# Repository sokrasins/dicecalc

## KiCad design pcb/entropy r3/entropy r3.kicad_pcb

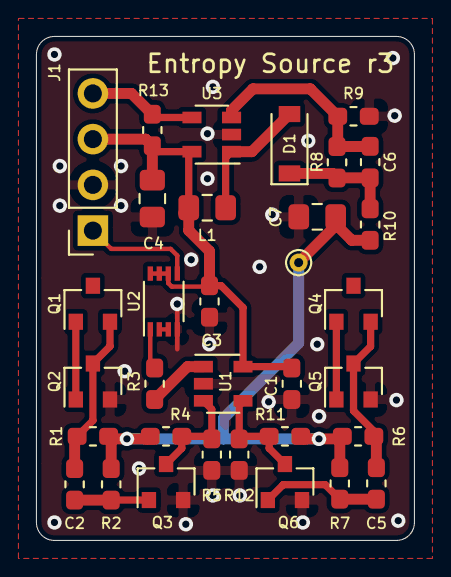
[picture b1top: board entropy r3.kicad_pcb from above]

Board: 2 copper layers, 21.0 x 28.0 mm, 33 parts (0 on the bottom side), 19 nets.

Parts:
C1, C2, C3, C5: 0.1u; C_0603_1608Metric_Pad1.05x0.95mm_HandSolder
C4, C7: 10u; C_0805_2012Metric_Pad1.15x1.40mm_HandSolder
C6: 22p; C_0603_1608Metric_Pad1.05x0.95mm_HandSolder
D1: MBR0530; D_SOD-123
J1: Conn_01x04_Female; PinSocket_1x04_P2.54mm_Vertical
L1: 10u; L_0805_2012Metric_Pad1.15x1.40mm_HandSolder
Q1, Q2, Q3, Q4, Q5, Q6: PMBT3904; SOT-23
R1, R4, R5, R6, R11, R12: 15k; R_0603_1608Metric_Pad1.05x0.95mm_HandSolder
R2, R7: 2.7M; R_0603_1608Metric_Pad1.05x0.95mm_HandSolder
R3, R13: 10k; R_0603_1608Metric_Pad1.05x0.95mm_HandSolder
R8: 2.2M; R_0603_1608Metric_Pad1.05x0.95mm_HandSolder
R9: 160k; R_0603_1608Metric_Pad1.05x0.95mm_HandSolder
R10: 0R; R_0603_1608Metric_Pad1.05x0.95mm_HandSolder
TP1: TestPoint; TestPoint_THTPad_D1.0mm_Drill0.5mm
U1: TLV3201; SOT-23-5
U2: NL17SZ74; VSSOP-8_2.3x2mm_P0.5mm
U3: TPS61041DDC; SOT-23-5

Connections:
+3V3: C1.1, C3.1, C4.1, J1.3, L1.1, R13.1, U1.5, U2.6, U2.7, U2.8, U3.5
ENABLE: J1.4, R13.2, U3.4
ENTROPY: J1.1, U2.5
GND: C1.2, C3.2, C4.2, C7.2, J1.2, Q2.2, Q3.2, Q5.2, Q6.2, R5.2, R9.2, R12.2, U1.2, U2.4, U3.2
NOISE_NEG: Q6.3, R11.2, R12.1, U1.4
NOISE_POS: Q3.3, R4.2, R5.1, U1.3
unnamed: C2.1, Q3.1, R2.2
unnamed: C2.2, Q1.2, Q2.3, R1.2
unnamed: C5.1, Q6.1, R7.2
unnamed: C5.2, Q4.2, Q5.3, R6.2
unnamed: C6.1, D1.1, R8.1, R10.2
unnamed: C6.2, R8.2, R9.1, U3.3
unnamed: D1.2, L1.2, U3.1
unnamed: Q1.1, Q2.1
unnamed: Q4.1, Q5.1
unnamed: R3.1, U2.1
unnamed: R3.2, U1.1
unnamed: U2.2, U2.3
VCC: C7.1, R1.1, R2.1, R4.1, R6.1, R7.1, R10.1, R11.1, TP1.1

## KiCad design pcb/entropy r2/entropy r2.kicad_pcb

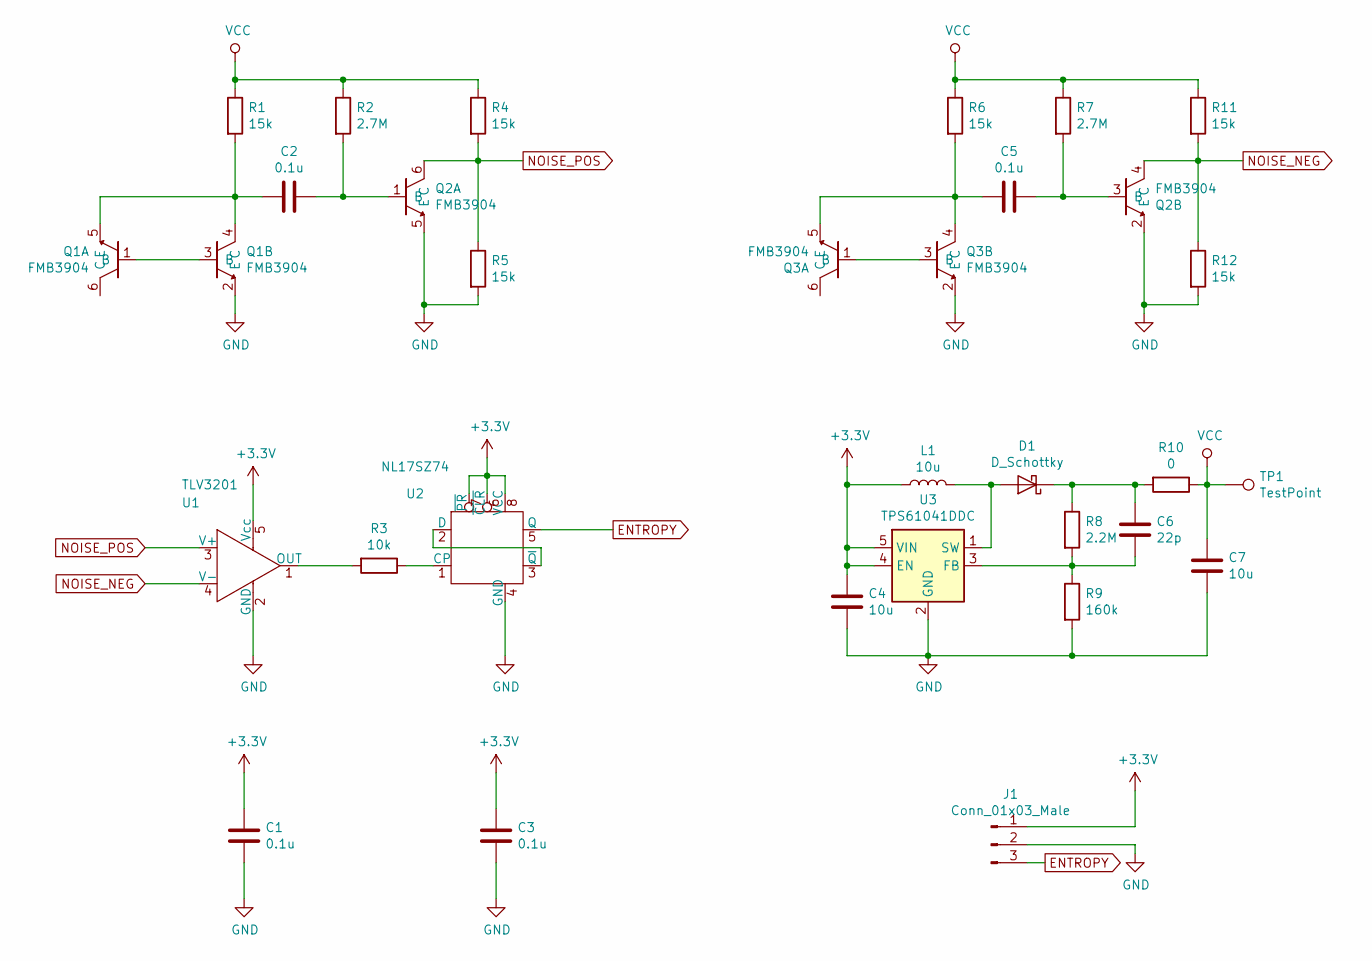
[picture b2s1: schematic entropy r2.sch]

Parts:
C1, C2, C3, C5: 0.1u; C_0603_1608Metric_Pad1.05x0.95mm_HandSolder
C4, C7: 10u; C_0805_2012Metric_Pad1.15x1.40mm_HandSolder
C6: 22p; C_0603_1608Metric_Pad1.05x0.95mm_HandSolder
D1: D_Schottky; D_SOD-123
J1: Conn_01x03_Male; PinHeader_1x03_P2.54mm_Vertical
L1: 10u; L_0805_2012Metric_Pad1.15x1.40mm_HandSolder
Q1, Q2, Q3: FMB3904; SuperSOT-6
R1, R4, R5, R6, R11, R12: 15k; R_0603_1608Metric_Pad1.05x0.95mm_HandSolder
R2, R7: 2.7M; R_0603_1608Metric_Pad1.05x0.95mm_HandSolder
R3: 10k; R_0603_1608Metric_Pad1.05x0.95mm_HandSolder
R8: 2.2M; R_0603_1608Metric_Pad1.05x0.95mm_HandSolder
R9: 160k; R_0603_1608Metric_Pad1.05x0.95mm_HandSolder
R10: 0; R_0603_1608Metric_Pad1.05x0.95mm_HandSolder
TP1: TestPoint; TestPoint_THTPad_D1.0mm_Drill0.5mm
U1: TLV3201; SOT-23-5
U2: NL17SZ74; VSSOP-8_2.3x2mm_P0.5mm
U3: TPS61041DDC; SOT-23-5

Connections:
+3V3: C1.1, C3.1, C4.1, J1.1, L1.1, U1.5 (Vcc), U2.6 (~CLR), U2.7 (~PR), U2.8 (VCC), U3.4 (EN), U3.5 (VIN)
ENTROPY: J1.3, U2.5 (Q)
GND: C1.2, C3.2, C4.2, C7.2, J1.2, Q1.2 (E), Q2.2 (E), Q2.5 (E), Q3.2 (E), R5.2, R9.2, R12.2, U1.2 (GND), U2.4 (GND), U3.2 (GND)
NOISE_NEG: Q2.4 (C), R11.2, R12.1, U1.4 (V-)
NOISE_POS: Q2.6 (C), R4.2, R5.1, U1.3 (V+)
unnamed: C2.1, Q2.1 (B), R2.2
unnamed: C2.2, Q1.4 (C), Q1.5 (E), R1.2
unnamed: C5.1, Q2.3 (B), R7.2
unnamed: C5.2, Q3.4 (C), Q3.5 (E), R6.2
unnamed: C6.1, D1.1 (K), R8.1, R10.2
unnamed: C6.2, R8.2, R9.1, U3.3 (FB)
unnamed: D1.2 (A), L1.2, U3.1 (SW)
unnamed: Q1.1 (B), Q1.3 (B)
unnamed: Q3.1 (B), Q3.3 (B)
unnamed: R3.1, U2.1 (CP)
unnamed: R3.2, U1.1 (OUT)
unnamed: U2.2 (D), U2.3 (~Q)
VCC: C7.1, R1.1, R2.1, R4.1, R6.1, R7.1, R10.1, R11.1, TP1.1

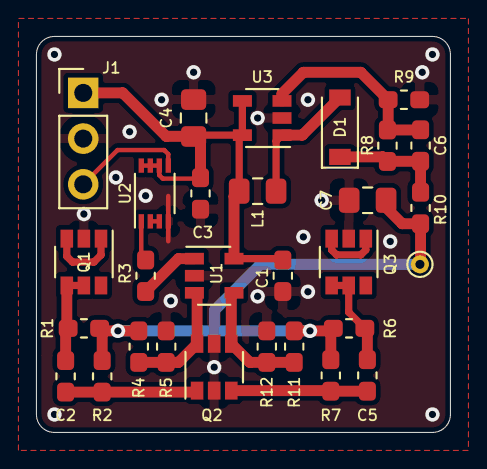
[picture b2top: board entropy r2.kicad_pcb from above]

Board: 2 copper layers, 23.0 x 22.0 mm, 29 parts (0 on the bottom side), 18 nets.

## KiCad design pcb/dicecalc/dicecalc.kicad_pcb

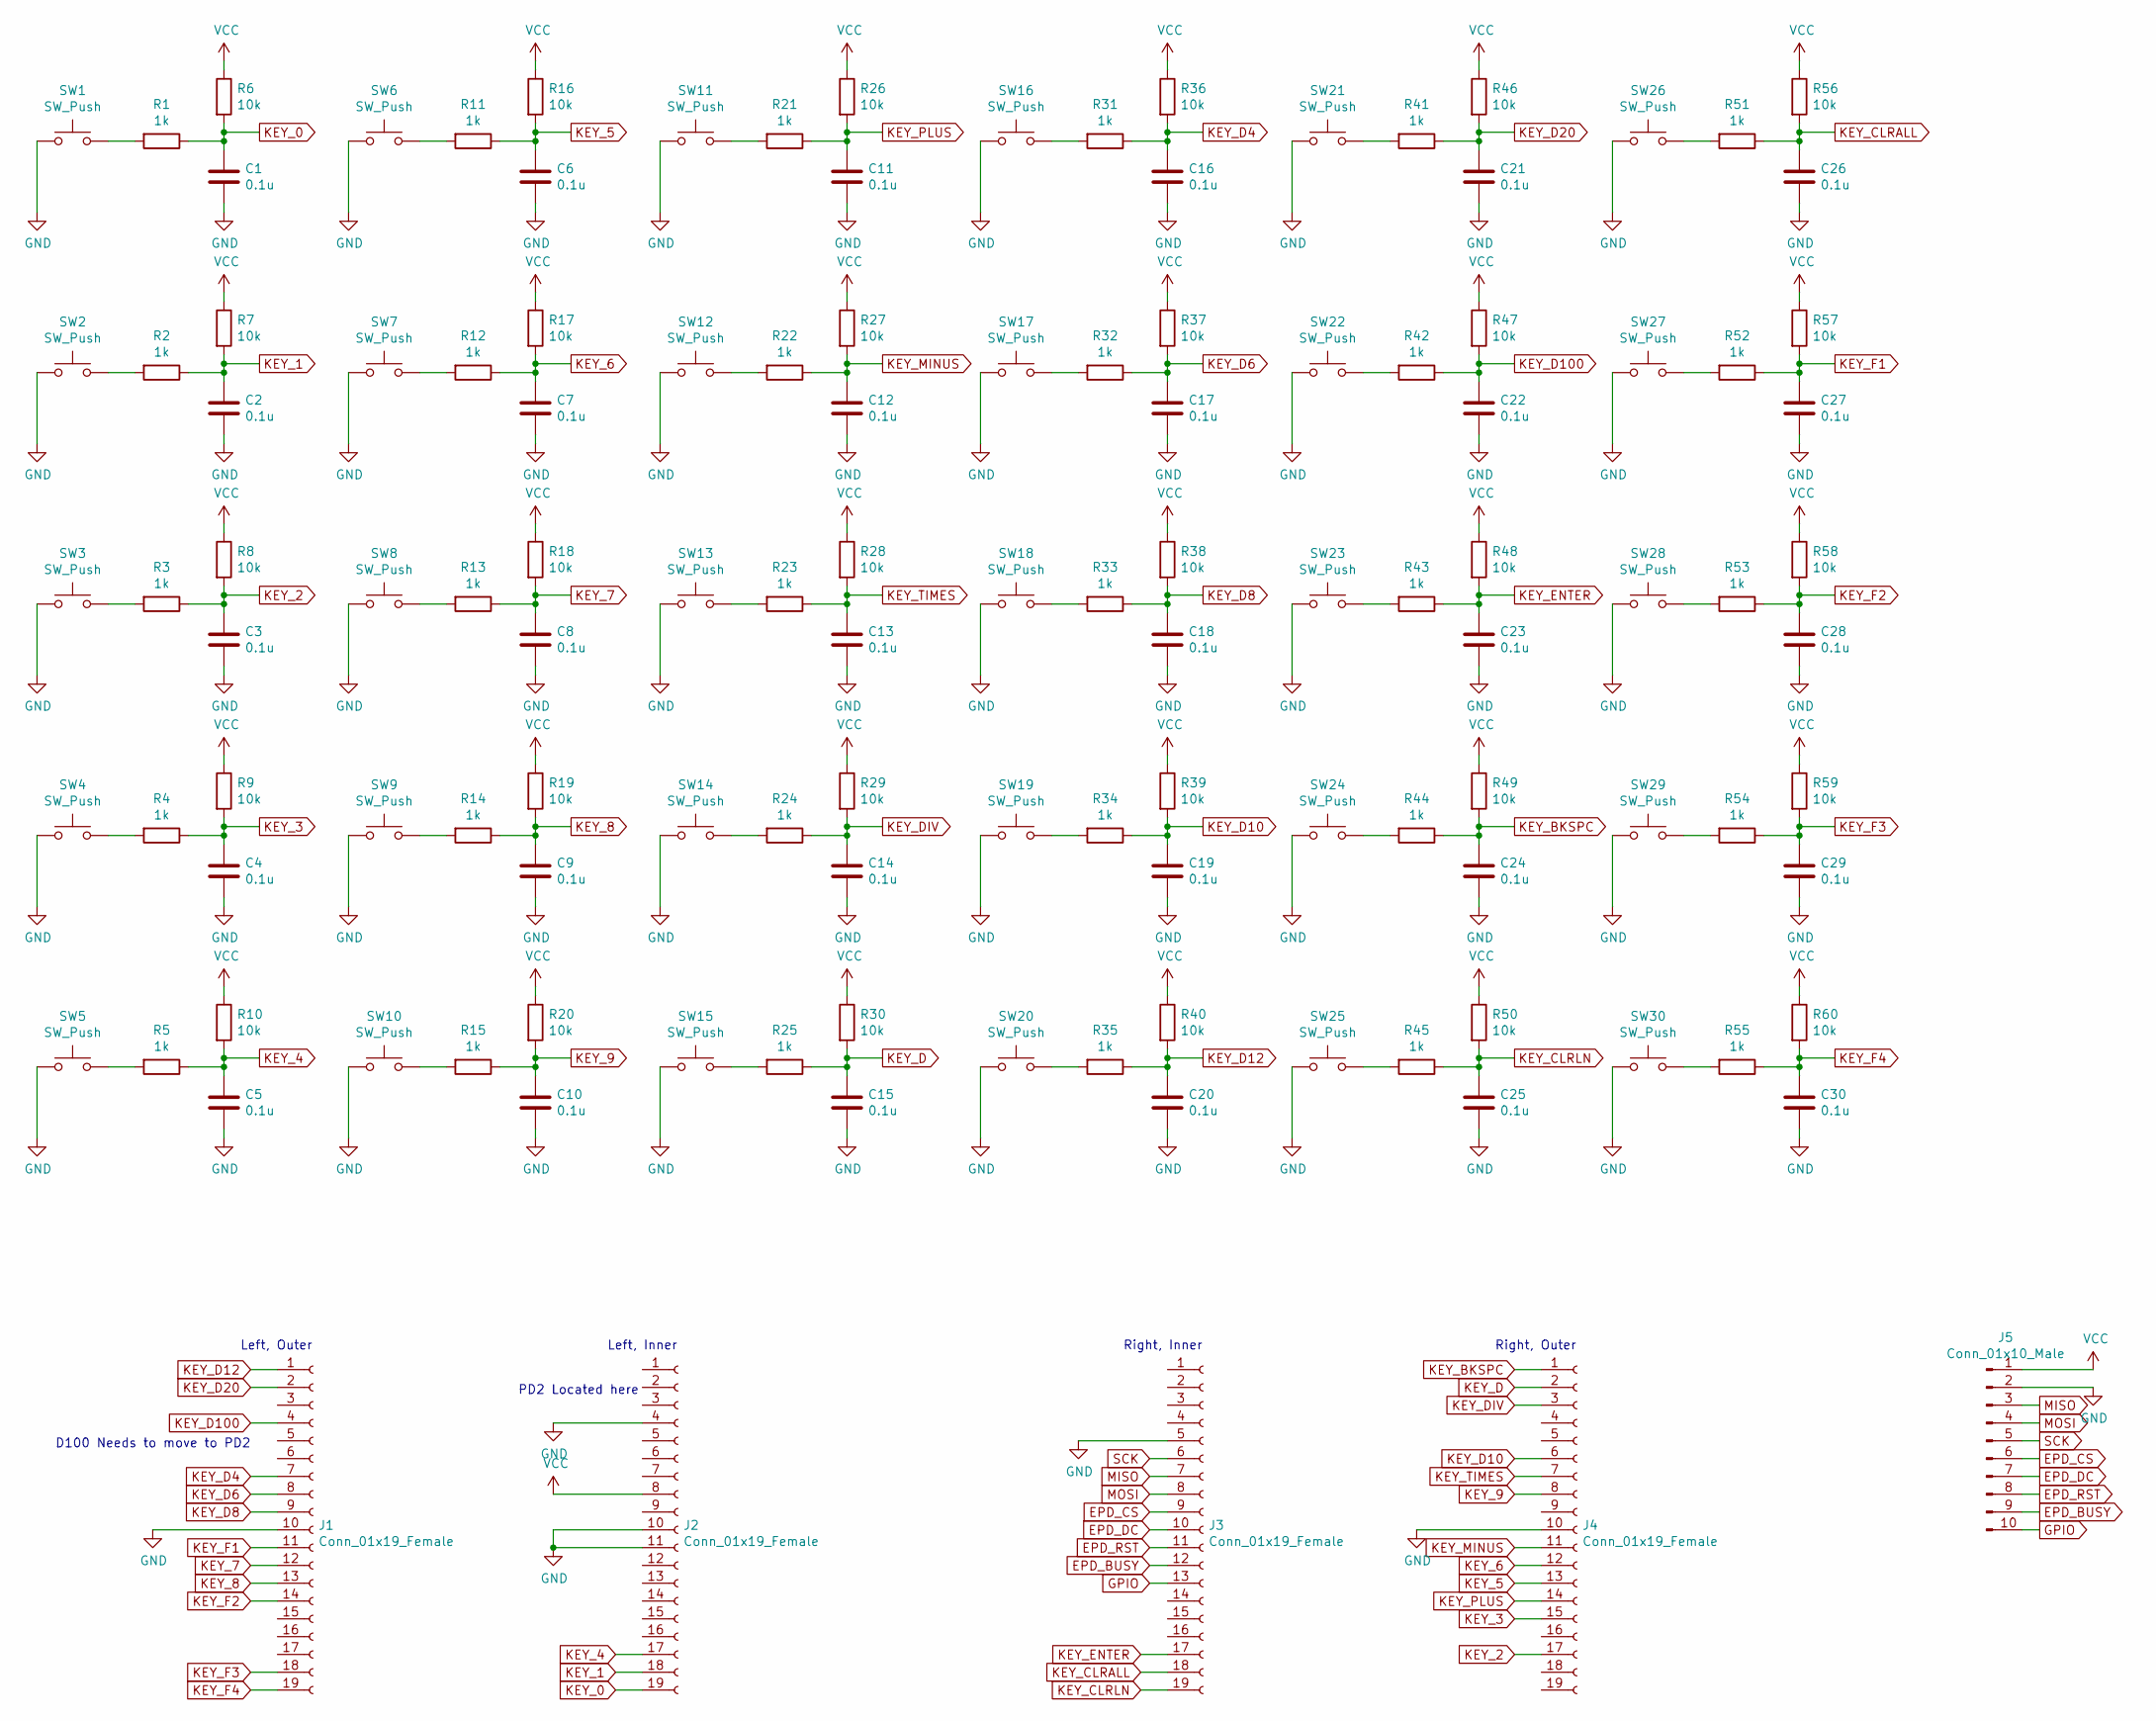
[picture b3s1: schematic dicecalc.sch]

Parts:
C1, C2, C3, C4, C5, C6, C7, C8, C9, C10, C11, C12, C13, C14, C15, C16, C17, C18, C19, C20, C21, C22, C23, C24, C25, C26, C27, C28, C29, C30: 0.1u; C_0603_1608Metric_Pad1.05x0.95mm_HandSolder
J1, J2, J3, J4: Conn_01x19_Female; PinSocket_1x19_P2.54mm_Vertical
J5: Conn_01x10_Male; PinSocket_1x10_P2.54mm_Horizontal
R1, R2, R3, R4, R5, R11, R12, R13, R14, R15, R21, R22, R23, R24, R25, R31, R32, R33, R34, R35, R41, R42, R43, R44, R45, R51, R52, R53, R54, R55: 1k; R_0603_1608Metric_Pad1.05x0.95mm_HandSolder
R6, R7, R8, R9, R10, R16, R17, R18, R19, R20, R26, R27, R28, R29, R30, R36, R37, R38, R39, R40, R46, R47, R48, R49, R50, R56, R57, R58, R59, R60: 10k; R_0603_1608Metric_Pad1.05x0.95mm_HandSolder
SW1, SW2, SW3, SW4, SW5, SW6, SW7, SW8, SW9, SW10, SW11, SW12, SW13, SW14, SW15, SW16, SW17, SW18, SW19, SW20, SW21, SW22, SW23, SW24, SW25, SW26, SW27, SW28, SW29, SW30: SW_Push; SW_Push_1P1T_NO_6x6mm_H9.5mm

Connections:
EPD_BUSY: J3.12, J5.9
EPD_CS: J3.9, J5.6
EPD_DC: J3.10, J5.7
EPD_RST: J3.11, J5.8
GND: C1.2, C2.2, C3.2, C4.2, C5.2, C6.2, C7.2, C8.2, C9.2, C10.2, C11.2, C12.2, C13.2, C14.2, C15.2, C16.2, C17.2, C18.2, C19.2, C20.2, C21.2, C22.2, C23.2, C24.2, C25.2, C26.2, C27.2, C28.2, C29.2, C30.2, J1.10, J2.4, J2.10, J2.11, J3.5, J4.10, J5.2, SW1.1, SW2.1, SW3.1, SW4.1, SW5.1, SW6.1, SW7.1, SW8.1, SW9.1, SW10.1, SW11.1, SW12.1, SW13.1, SW14.1, SW15.1, SW16.1, SW17.1, SW18.1, SW19.1, SW20.1, SW21.1, SW22.1, SW23.1, SW24.1, SW25.1, SW26.1, SW27.1, SW28.1, SW29.1, SW30.1
GPIO: J3.13, J5.10
KEY_0: C1.1, J2.19, R1.1, R6.2
KEY_1: C2.1, J2.18, R2.1, R7.2
KEY_2: C3.1, J4.17, R3.1, R8.2
KEY_3: C4.1, J4.15, R4.1, R9.2
KEY_4: C5.1, J2.17, R5.1, R10.2
KEY_5: C6.1, J4.13, R11.1, R16.2
KEY_6: C7.1, J4.12, R12.1, R17.2
KEY_7: C8.1, J1.12, R13.1, R18.2
KEY_8: C9.1, J1.13, R14.1, R19.2
KEY_9: C10.1, J4.8, R15.1, R20.2
KEY_BKSPC: C24.1, J4.1, R44.1, R49.2
KEY_CLRALL: C26.1, J3.18, R51.1, R56.2
KEY_CLRLN: C25.1, J3.19, R45.1, R50.2
KEY_D: C15.1, J4.2, R25.1, R30.2
KEY_D4: C16.1, J1.7, R31.1, R36.2
KEY_D6: C17.1, J1.8, R32.1, R37.2
KEY_D8: C18.1, J1.9, R33.1, R38.2
KEY_D10: C19.1, J4.6, R34.1, R39.2
KEY_D12: C20.1, J1.1, R35.1, R40.2
KEY_D20: C21.1, J1.2, R41.1, R46.2
KEY_D100: C22.1, J1.4, R42.1, R47.2
KEY_DIV: C14.1, J4.3, R24.1, R29.2
KEY_ENTER: C23.1, J3.17, R43.1, R48.2
KEY_F1: C27.1, J1.11, R52.1, R57.2
KEY_F2: C28.1, J1.14, R53.1, R58.2
KEY_F3: C29.1, J1.18, R54.1, R59.2
KEY_F4: C30.1, J1.19, R55.1, R60.2
KEY_MINUS: C12.1, J4.11, R22.1, R27.2
KEY_PLUS: C11.1, J4.14, R21.1, R26.2
KEY_TIMES: C13.1, J4.7, R23.1, R28.2
MISO: J3.7, J5.3
MOSI: J3.8, J5.4
unnamed: R1.2, SW1.2
unnamed: R2.2, SW2.2
unnamed: R3.2, SW3.2
unnamed: R4.2, SW4.2
unnamed: R5.2, SW5.2
unnamed: R11.2, SW6.2
unnamed: R12.2, SW7.2
unnamed: R13.2, SW8.2
unnamed: R14.2, SW9.2
unnamed: R15.2, SW10.2
unnamed: R21.2, SW11.2
unnamed: R22.2, SW12.2
unnamed: R23.2, SW13.2
unnamed: R24.2, SW14.2
unnamed: R25.2, SW15.2
unnamed: R31.2, SW16.2
unnamed: R32.2, SW17.2
unnamed: R33.2, SW18.2
unnamed: R34.2, SW19.2
unnamed: R35.2, SW20.2
unnamed: R41.2, SW21.2
unnamed: R42.2, SW22.2
unnamed: R43.2, SW23.2
unnamed: R44.2, SW24.2
unnamed: R45.2, SW25.2
unnamed: R51.2, SW26.2
unnamed: R52.2, SW27.2
unnamed: R53.2, SW28.2
unnamed: R54.2, SW29.2
unnamed: R55.2, SW30.2
SCK: J3.6, J5.5
VCC: J2.8, J5.1, R6.1, R7.1, R8.1, R9.1, R10.1, R16.1, R17.1, R18.1, R19.1, R20.1, R26.1, R27.1, R28.1, R29.1, R30.1, R36.1, R37.1, R38.1, R39.1, R40.1, R46.1, R47.1, R48.1, R49.1, R50.1, R56.1, R57.1, R58.1, R59.1, R60.1

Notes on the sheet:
Left, Outer
Left, Inner
Right, Inner
Right, Outer
D100 Needs to move to PD2
PD2 Located here

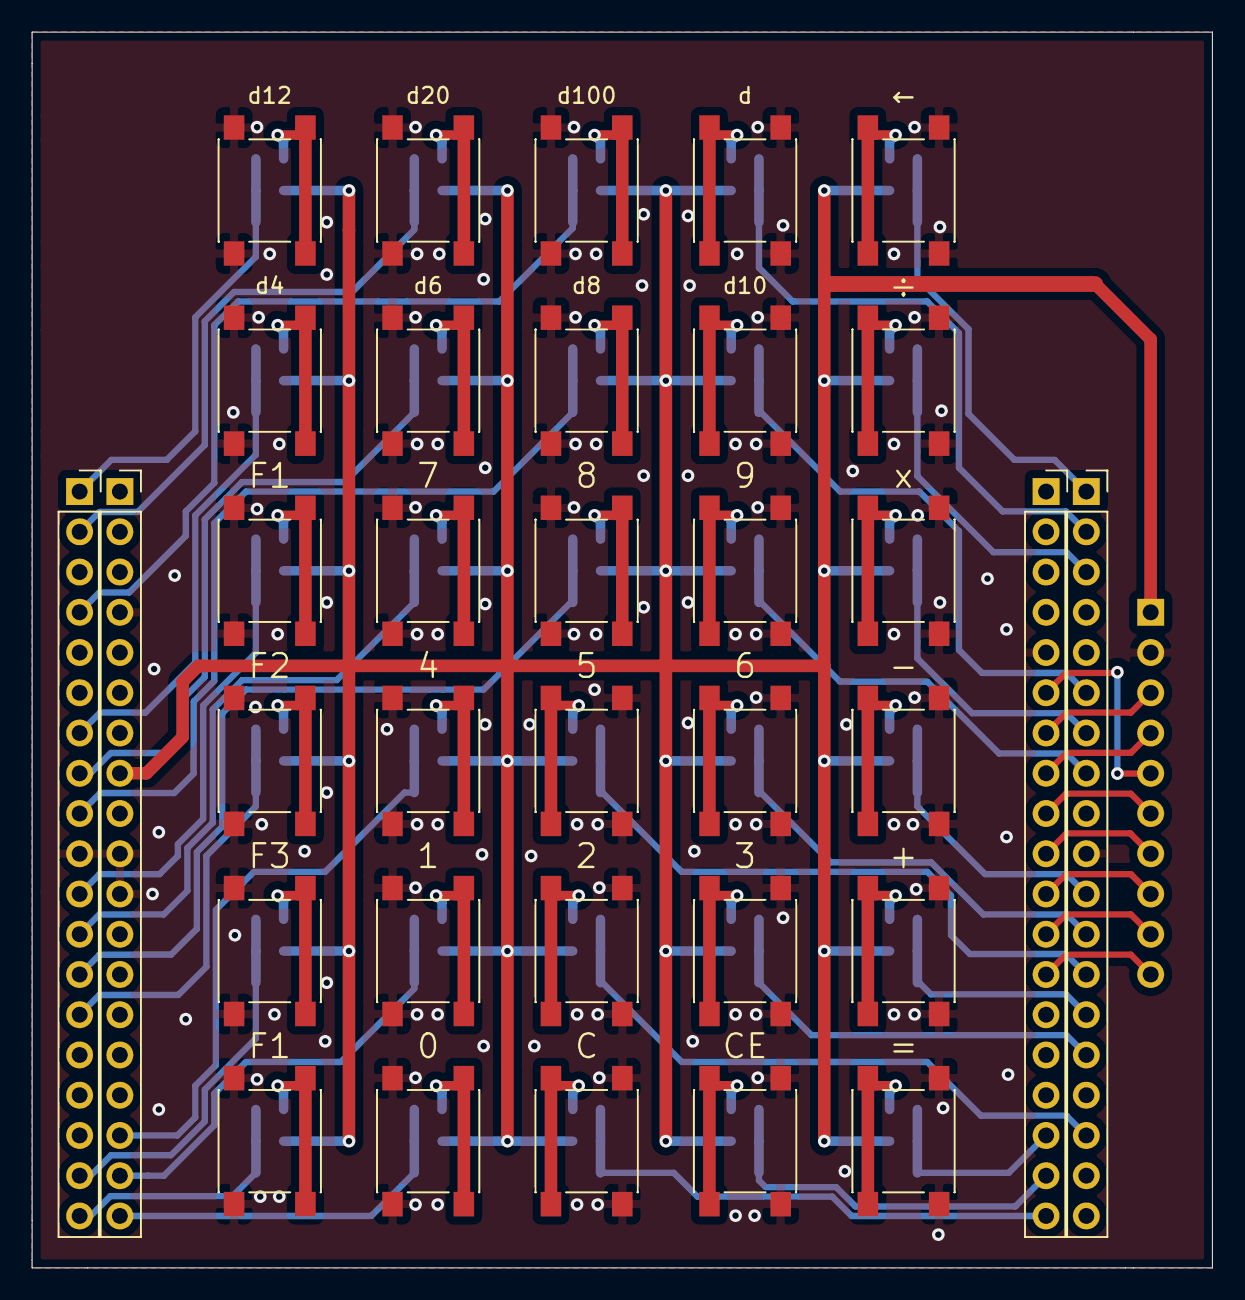
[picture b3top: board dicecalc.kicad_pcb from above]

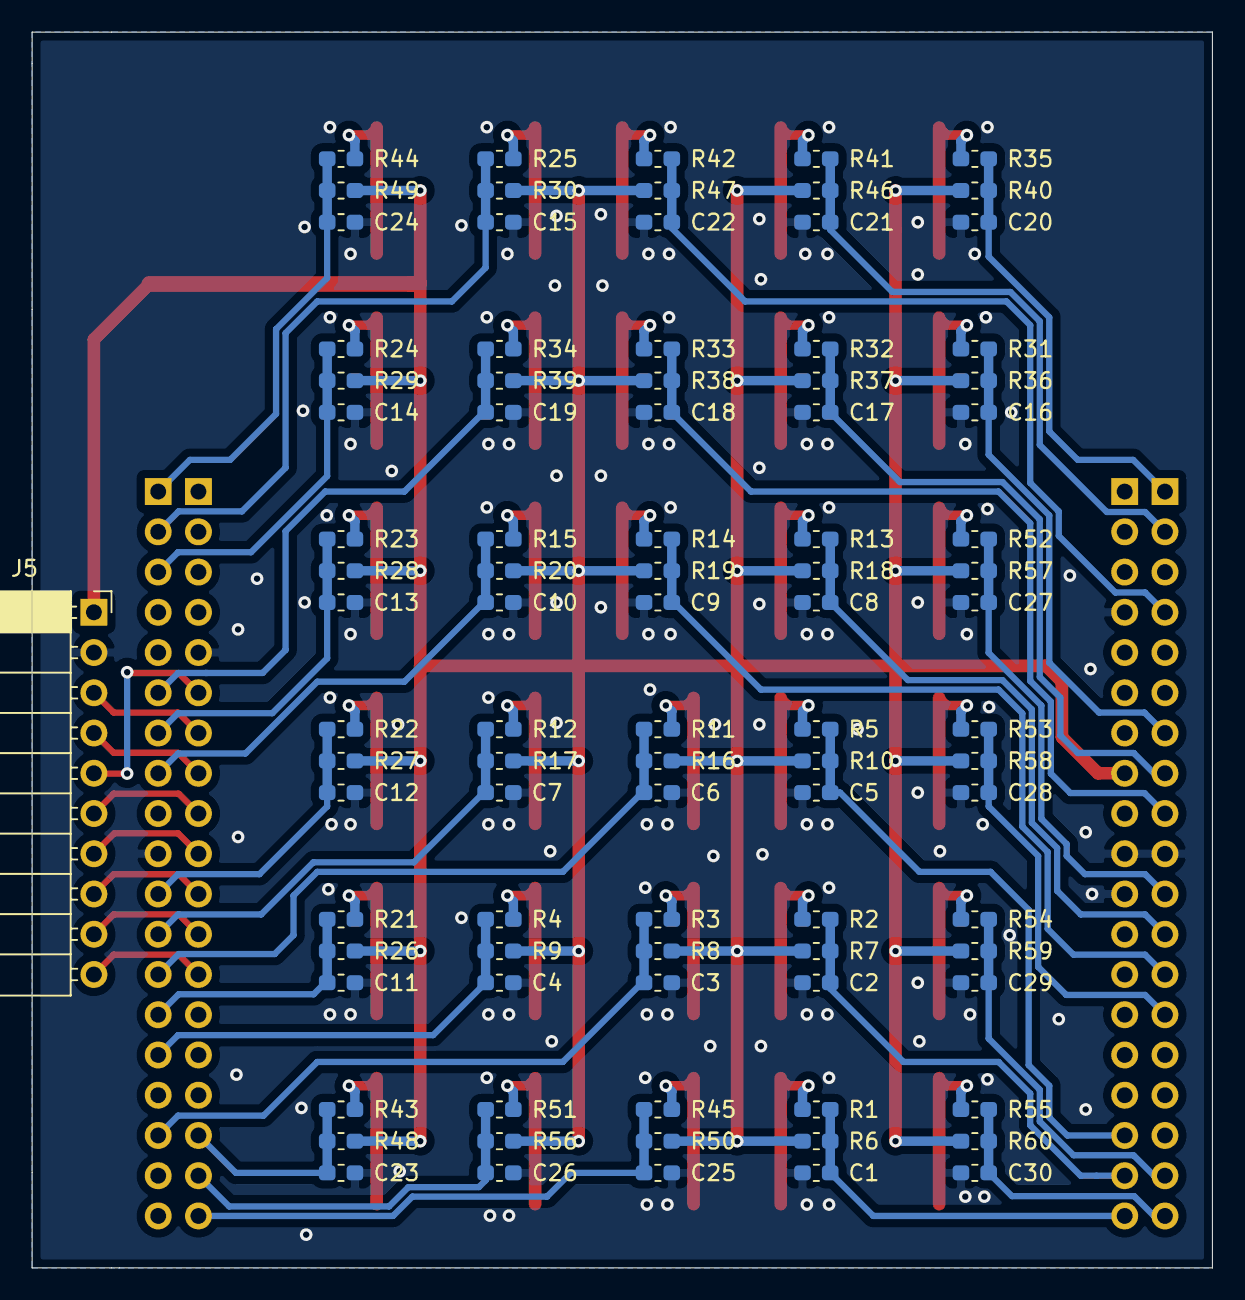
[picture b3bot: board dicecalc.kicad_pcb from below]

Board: 2 copper layers, 74.5 x 78.0 mm, 125 parts (91 on the bottom side), 70 nets.

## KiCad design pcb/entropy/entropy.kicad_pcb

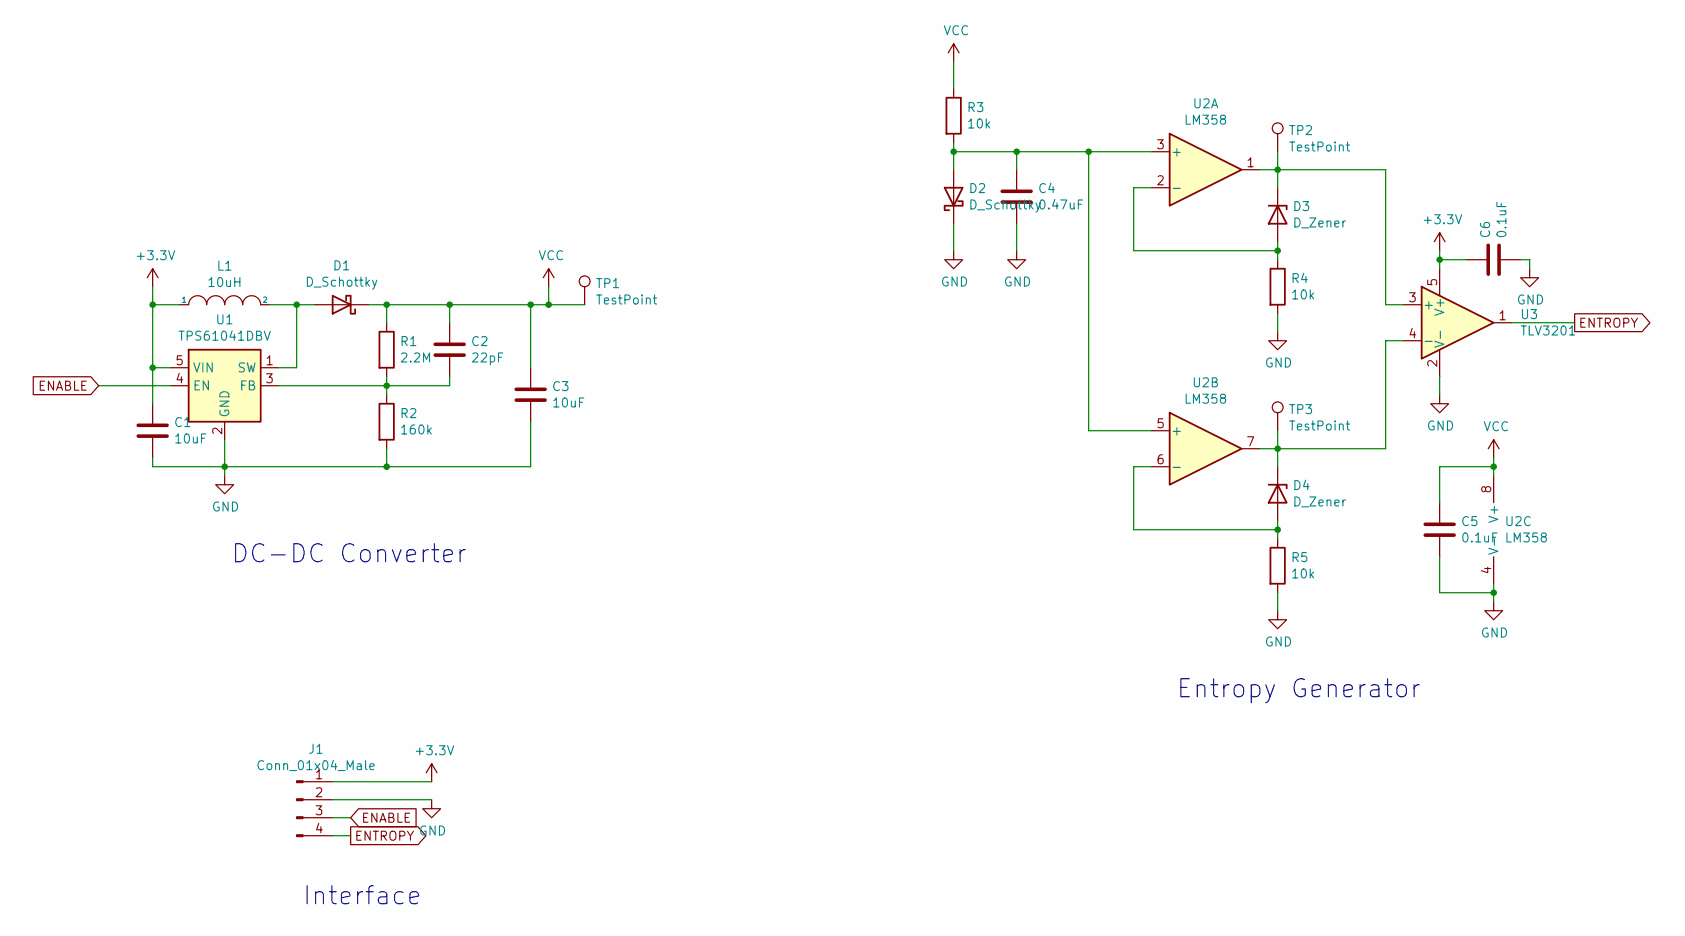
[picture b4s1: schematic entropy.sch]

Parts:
C1, C3: 10uF; C_0805_2012Metric_Pad1.15x1.40mm_HandSolder
C2: 22pF; C_0603_1608Metric_Pad1.05x0.95mm_HandSolder
C4: 0.47uF; C_0603_1608Metric_Pad1.05x0.95mm_HandSolder
C5, C6: 0.1uF; C_0603_1608Metric_Pad1.05x0.95mm_HandSolder
D1, D2: D_Schottky; D_SOD-123
D3, D4: D_Zener; D_DO-35_SOD27_P7.62mm_Horizontal
J1: Conn_01x04_Male; PinSocket_1x04_P2.54mm_Vertical
L1: 10uH; L_0805_2012Metric_Pad1.15x1.40mm_HandSolder
R1: 2.2M; R_0603_1608Metric_Pad1.05x0.95mm_HandSolder
R2: 160k; R_0603_1608Metric_Pad1.05x0.95mm_HandSolder
R3, R4, R5: 10k; R_0603_1608Metric_Pad1.05x0.95mm_HandSolder
TP1, TP2, TP3: TestPoint; TestPoint_THTPad_D1.0mm_Drill0.5mm
U1: TPS61041DBV; SOT-23-5
U2: LM358; SOIC-8_3.9x4.9mm_P1.27mm
U3: TLV3201; SOT-23-5

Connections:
+3V3: C1.1, C6.1, J1.1, L1.1, U1.5 (VIN), U3.5 (V+)
ENABLE: J1.3, U1.4 (EN)
ENTROPY: J1.4, U3.1
GND: C1.2, C3.2, C4.2, C5.2, C6.2, D2.1 (K), J1.2, R2.2, R4.2, R5.2, U1.2 (GND), U2.4 (V-), U3.2 (V-)
unnamed: C2.2, R1.2, R2.1, U1.3 (FB)
unnamed: C4.1, D2.2 (A), R3.2, U2.3 (+), U2.5 (+)
unnamed: D1.2 (A), L1.2, U1.1 (SW)
unnamed: D3.1 (K), TP2.1, U2.1, U3.3 (+)
unnamed: D3.2 (A), R4.1, U2.2 (-)
unnamed: D4.1 (K), TP3.1, U2.7, U3.4 (-)
unnamed: D4.2 (A), R5.1, U2.6 (-)
VCC: C2.1, C3.1, C5.1, D1.1 (K), R1.1, R3.1, TP1.1, U2.8 (V+)

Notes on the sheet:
DC-DC Converter
Interface
Entropy Generator

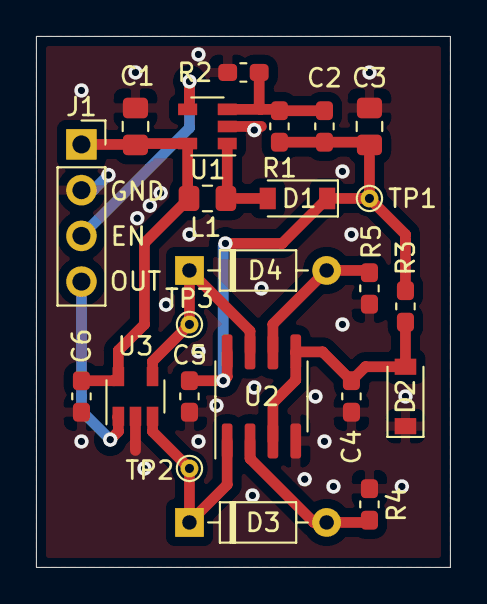
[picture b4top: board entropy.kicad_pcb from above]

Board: 2 copper layers, 23.0 x 29.5 mm, 23 parts (0 on the bottom side), 12 nets.

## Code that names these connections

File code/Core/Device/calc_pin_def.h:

/*
 * calc_pin_def.h
 *
 *  Created on: Jan 5, 2021
 *      Author: sok
 */

#ifndef DEVICE_CALC_PIN_DEF_H_
#define DEVICE_CALC_PIN_DEF_H_

#include "stm32f4xx_hal.h"

// Define pins for debug UART port
#define DEBUG_USART_PORT GPIOA
#define DEBUG_USART_TX_Pin GPIO_PIN_2
#define DEBUG_USART_RX_Pin GPIO_PIN_3

// Entropy source pins
#define ENT_SOURCE_PORT	GPIOD
#define ENT_SOURCE_PIN	GPIO_PIN_2

#define ENT_EN_PORT		GPIOC
#define ENT_EN_PIN		GPIO_PIN_11

// E-paper display pins
#define EPD_RST_PORT    GPIOB
#define EPD_RST_PIN 	GPIO_PIN_8

#define EPD_DC_PORT     GPIOC
#define EPD_DC_PIN 		GPIO_PIN_6

#define EPD_CS_PORT		GPIOC
#define EPD_CS_PIN 		GPIO_PIN_8

#define EPD_BUSY_PORT   GPIOC
#define EPD_BUSY_PIN 	GPIO_PIN_9

#define EPD_SPI_PORT	GPIOA
#define EPD_SCK_PIN		GPIO_PIN_5
#define EPD_MOSI_PIN	GPIO_PIN_7
#define EPD_MISO_PIN	GPIO_PIN_6

// Keypad pins
#define KEY_0_PORT		GPIOC
#define KEY_0_PIN		GPIO_PIN_0

#define KEY_1_PORT		GPIOC
#define KEY_1_PIN		GPIO_PIN_1

#define KEY_2_PORT		GPIOB
#define KEY_2_PIN		GPIO_PIN_5

#define KEY_3_PORT		GPIOB
#define KEY_3_PIN		GPIO_PIN_13

#define KEY_4_PORT		GPIOB
#define KEY_4_PIN		GPIO_PIN_0

#define KEY_5_PORT		GPIOB
#define KEY_5_PIN		GPIO_PIN_14

#define KEY_6_PORT		GPIOB
#define KEY_6_PIN		GPIO_PIN_10

#define KEY_7_PORT		GPIOA
#define KEY_7_PIN		GPIO_PIN_0

#define KEY_8_PORT		GPIOA
#define KEY_8_PIN		GPIO_PIN_1

#define KEY_9_PORT		GPIOA
#define KEY_9_PIN		GPIO_PIN_8

#define KEY_F1_PORT		GPIOC
#define KEY_F1_PIN		GPIO_PIN_15

#define KEY_F2_PORT		GPIOA
#define KEY_F2_PIN		GPIO_PIN_4

#define KEY_F3_PORT		GPIOC
#define KEY_F3_PIN		GPIO_PIN_2

#define KEY_F4_PORT		GPIOC
#define KEY_F4_PIN		GPIO_PIN_3

#define KEY_PLUS_PORT	GPIOB
#define KEY_PLUS_PIN	GPIO_PIN_4

#define KEY_MINUS_PORT	GPIOB
#define KEY_MINUS_PIN	GPIO_PIN_15

#define KEY_TIMES_PORT	GPIOA
#define KEY_TIMES_PIN	GPIO_PIN_9

#define KEY_DIV_PORT	GPIOB
#define KEY_DIV_PIN		GPIO_PIN_6

#define KEY_D_PORT		GPIOB
#define KEY_D_PIN		GPIO_PIN_12

#define KEY_D4_PORT		GPIOB
#define KEY_D4_PIN		GPIO_PIN_7

#define KEY_D6_PORT		GPIOC
#define KEY_D6_PIN		GPIO_PIN_13

#define KEY_D8_PORT		GPIOC
#define KEY_D8_PIN		GPIO_PIN_14

#define KEY_D10_PORT	GPIOC
#define KEY_D10_PIN		GPIO_PIN_7

#define KEY_D12_PORT	GPIOC
#define KEY_D12_PIN		GPIO_PIN_10

#define KEY_D20_PORT	GPIOC
#define KEY_D20_PIN		GPIO_PIN_12

#define KEY_D100_PORT	GPIOA
#define KEY_D100_PIN	GPIO_PIN_15

#define KEY_ENTER_PORT	GPIOB
#define KEY_ENTER_PIN	GPIO_PIN_3

#define KEY_CLRALL_PORT	GPIOC
#define KEY_CLRALL_PIN	GPIO_PIN_4

#define KEY_CLRLINE_PORT GPIOA
#define KEY_CLRLINE_PIN	GPIO_PIN_10

#define KEY_BKSPC_PORT	GPIOA
#define KEY_BKSPC_PIN	GPIO_PIN_11

#endif /* DEVICE_CALC_PIN_DEF_H_ */

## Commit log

2021-01-07 Add gitignore
2021-01-07 update gitignore
2021-01-07 Add code
2021-01-07 Ignore python
2021-01-07 Add python serial reader
2021-01-07 Note pins that need to move
2021-01-07 Add spi stuff
2021-01-08 Spi object sending data now
2021-01-08 started entropy interface
2021-01-08 Added timer to entropy
2021-01-09 Add random test
2021-01-14 Add epaper basics
2021-01-15 Port graphics to cpp
2021-01-15 Eval dice rolls if it's the last in the expression
2021-01-16 Port to new keyboard, add key functionality
2021-01-16 Try to change keys to exti, but not enough ISR lines
2021-01-16 poll keyboard in ISR
2021-01-16 Re-eval last expr when pressing enter on an empty line
2021-07-17 push everything
2021-07-24 Add latest rev and entropy collection script
2021-07-24 Add histogram viewer, add args to entropy collection
2021-07-24 Add param log, calc bytes in callback
2021-07-24 Plot histogram as data is being collected
2021-07-25 fix histogram display issue
2021-07-25 Add bin filedx to gitignore
2021-08-07 Added new datasheets
2021-08-12 Move old project
2021-08-12 Move stm code folder
2021-08-12 Add development tests
2021-08-12 Add ffc/fpc lib
2021-08-12 Add atsaml10 code
2021-08-15 Added xplained board docs and pick better starting proj
2021-08-15 Rename project
2021-08-15 Write pseudocode for main"
2021-08-15 Add new pcb revs
2021-08-15 Resolve conflicts
2021-09-18 Added script to collect entropy from new circuit
2021-10-08 add test code :
